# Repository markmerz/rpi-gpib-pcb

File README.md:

# rpi-gpib-pcb
PCB for a Raspberry Pi GPIB board.

Different PCB layout for a electronomikon's Raspberry Pi GPIB shield design at https://github.com/elektronomikon/raspi_gpib_shield/.

This board is 100x100mm and connects to the RPI with 2x20 ribbon cable. Designed to fit into particular milled aluminum box I had lying around. RPI has VXI11 server which exposes GPIB to the network.

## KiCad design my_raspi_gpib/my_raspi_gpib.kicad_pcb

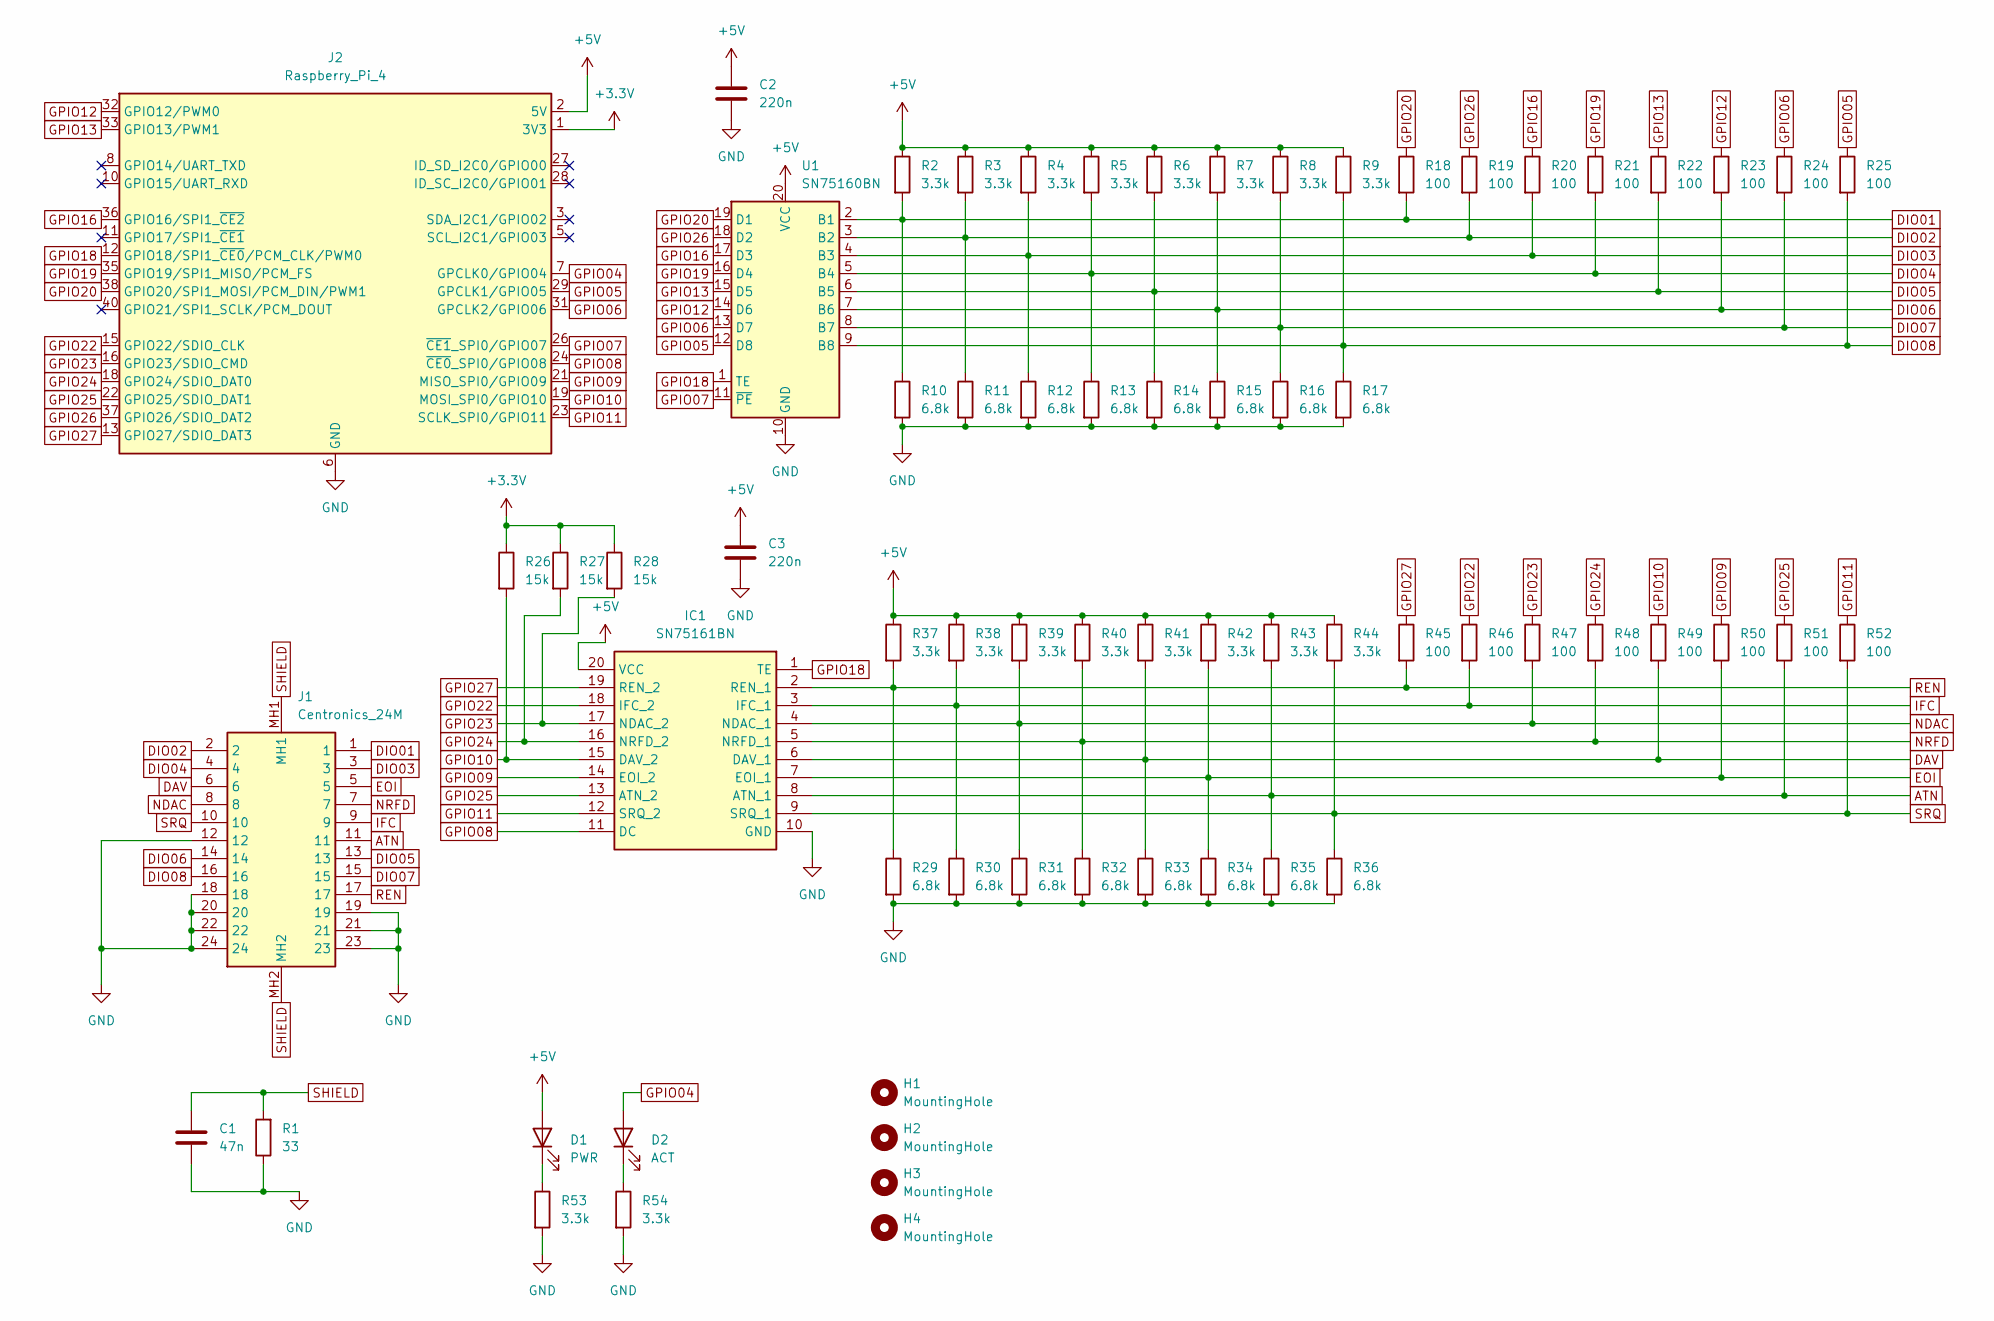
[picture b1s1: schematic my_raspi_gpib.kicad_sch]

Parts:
C1: 47n; C_Disc_D3.8mm_W2.6mm_P2.50mm
C2, C3: 220n; C_Disc_D3.8mm_W2.6mm_P2.50mm
D1: PWR; LED_D3.0mm
D2: ACT; LED_D3.0mm
H1, H2, H3, H4: MountingHole; MountingHole_3.2mm_M3
IC1: SN75161BN; DIP-20_W7.62mm; Manufacturer_Part_Number SN75161BN
J1: Centronics_24M; Manufacturer_Part_Number DS1079-F240BS
J2: Raspberry_Pi_4; PinHeader_2x20_P2.54mm_Vertical
R1: 33; R_Axial_DIN0207_L6.3mm_D2.5mm_P2.54mm_Vertical
R2, R3, R4, R5, R6, R7, R8, R9, R37, R38, R39, R40, R41, R42, R43, R44, R53, R54: 3.3k; R_Axial_DIN0207_L6.3mm_D2.5mm_P2.54mm_Vertical
R10, R11, R12, R13, R14, R15, R16, R17, R29, R30, R31, R32, R33, R34, R35, R36: 6.8k; R_Axial_DIN0207_L6.3mm_D2.5mm_P2.54mm_Vertical
R18, R19, R20, R21, R22, R23, R24, R25, R45, R46, R47, R48, R49, R50, R51, R52: 100; R_Axial_DIN0207_L6.3mm_D2.5mm_P2.54mm_Vertical
R26, R27, R28: 15k; R_Axial_DIN0207_L6.3mm_D2.5mm_P2.54mm_Vertical
U1: SN75160BN; DIP-20_W7.62mm

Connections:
+3.3V: J2.1 (3V3), J2.17 (3V3), R26.1, R27.1, R28.1
+5V: C2.1, C3.1, D1.2 (A), IC1.20 (VCC), J2.2 (5V), J2.4 (5V), R2.1, R3.1, R4.1, R5.1, R6.1, R7.1, R8.1, R9.1, R37.1, R38.1, R39.1, R40.1, R41.1, R42.1, R43.1, R44.1, U1.20 (VCC)
ATN: IC1.8 (ATN_1), J1.11, R35.1, R43.2, R51.2
DAV: IC1.6 (DAV_1), J1.6, R33.1, R41.2, R49.2
DIO01: J1.1, R2.2, R10.1, R18.2, U1.2 (B1)
DIO02: J1.2, R3.2, R11.1, R19.2, U1.3 (B2)
DIO03: J1.3, R4.2, R12.1, R20.2, U1.4 (B3)
DIO04: J1.4, R5.2, R13.1, R21.2, U1.5 (B4)
DIO05: J1.13, R6.2, R14.1, R22.2, U1.6 (B5)
DIO06: J1.14, R7.2, R15.1, R23.2, U1.7 (B6)
DIO07: J1.15, R8.2, R16.1, R24.2, U1.8 (B7)
DIO08: J1.16, R9.2, R17.1, R25.2, U1.9 (B8)
EOI: IC1.7 (EOI_1), J1.5, R34.1, R42.2, R50.2
GND: C1.1, C2.2, C3.2, IC1.10 (GND), J1.12, J1.18, J1.19, J1.20, J1.21, J1.22, J1.23, J1.24, J2.6 (GND), J2.9 (GND), J2.14 (GND), J2.20 (GND), J2.25 (GND), J2.30 (GND), J2.34 (GND), J2.39 (GND), R1.1, R10.2, R11.2, R12.2, R13.2, R14.2, R15.2, R16.2, R17.2, R29.2, R30.2, R31.2, R32.2, R33.2, R34.2, R35.2, R36.2, R53.2, R54.2, U1.10 (GND)
GPIO02: J2.3 (SDA_I2C1/GPIO02)
GPIO03: J2.5 (SCL_I2C1/GPIO03)
GPIO04: D2.2 (A), J2.7 (GPCLK0/GPIO04)
GPIO05: J2.29 (GPCLK1/GPIO05), R25.1, U1.12 (D8)
GPIO06: J2.31 (GPCLK2/GPIO06), R24.1, U1.13 (D7)
GPIO07: J2.26 (~CE1_SPI0/GPIO07), U1.11 (~PE)
GPIO08: IC1.11 (DC), J2.24 (~CE0_SPI0/GPIO08)
GPIO09: IC1.14 (EOI_2), J2.21 (MISO_SPI0/GPIO09), R50.1
GPIO10: IC1.15 (DAV_2), J2.19 (MOSI_SPI0/GPIO10), R26.2, R49.1
GPIO11: IC1.12 (SRQ_2), J2.23 (SCLK_SPI0/GPIO11), R52.1
GPIO12: J2.32 (GPIO12/PWM0), R23.1, U1.14 (D6)
GPIO13: J2.33 (GPIO13/PWM1), R22.1, U1.15 (D5)
GPIO14: J2.8 (GPIO14/UART_TXD)
GPIO15: J2.10 (GPIO15/UART_RXD)
GPIO16: J2.36 (GPIO16/SPI1_~CE2), R20.1, U1.17 (D3)
GPIO17: J2.11 (GPIO17/SPI1_~CE1)
GPIO18: IC1.1 (TE), J2.12 (GPIO18/SPI1_~CE0/PCM_CLK/PWM0), U1.1 (TE)
GPIO19: J2.35 (GPIO19/SPI1_MISO/PCM_FS), R21.1, U1.16 (D4)
GPIO20: J2.38 (GPIO20/SPI1_MOSI/PCM_DIN/PWM1), R18.1, U1.19 (D1)
GPIO21: J2.40 (GPIO21/SPI1_SCLK/PCM_DOUT)
GPIO22: IC1.18 (IFC_2), J2.15 (GPIO22/SDIO_CLK), R46.1
GPIO23: IC1.17 (NDAC_2), J2.16 (GPIO23/SDIO_CMD), R28.2, R47.1
GPIO24: IC1.16 (NRFD_2), J2.18 (GPIO24/SDIO_DAT0), R27.2, R48.1
GPIO25: IC1.13 (ATN_2), J2.22 (GPIO25/SDIO_DAT1), R51.1
GPIO26: J2.37 (GPIO26/SDIO_DAT2), R19.1, U1.18 (D2)
GPIO27: IC1.19 (REN_2), J2.13 (GPIO27/SDIO_DAT3), R45.1
IFC: IC1.3 (IFC_1), J1.9, R30.1, R38.2, R46.2
NDAC: IC1.4 (NDAC_1), J1.8, R31.1, R39.2, R47.2
NRFD: IC1.5 (NRFD_1), J1.7, R32.1, R40.2, R48.2
unnamed: D1.1 (K), R53.1
unnamed: D2.1 (K), R54.1
REN: IC1.2 (REN_1), J1.17, R29.1, R37.2, R45.2
SHIELD: C1.2, J1.MH1, J1.MH2, R1.2
SRQ: IC1.9 (SRQ_1), J1.10, R36.1, R44.2, R52.2

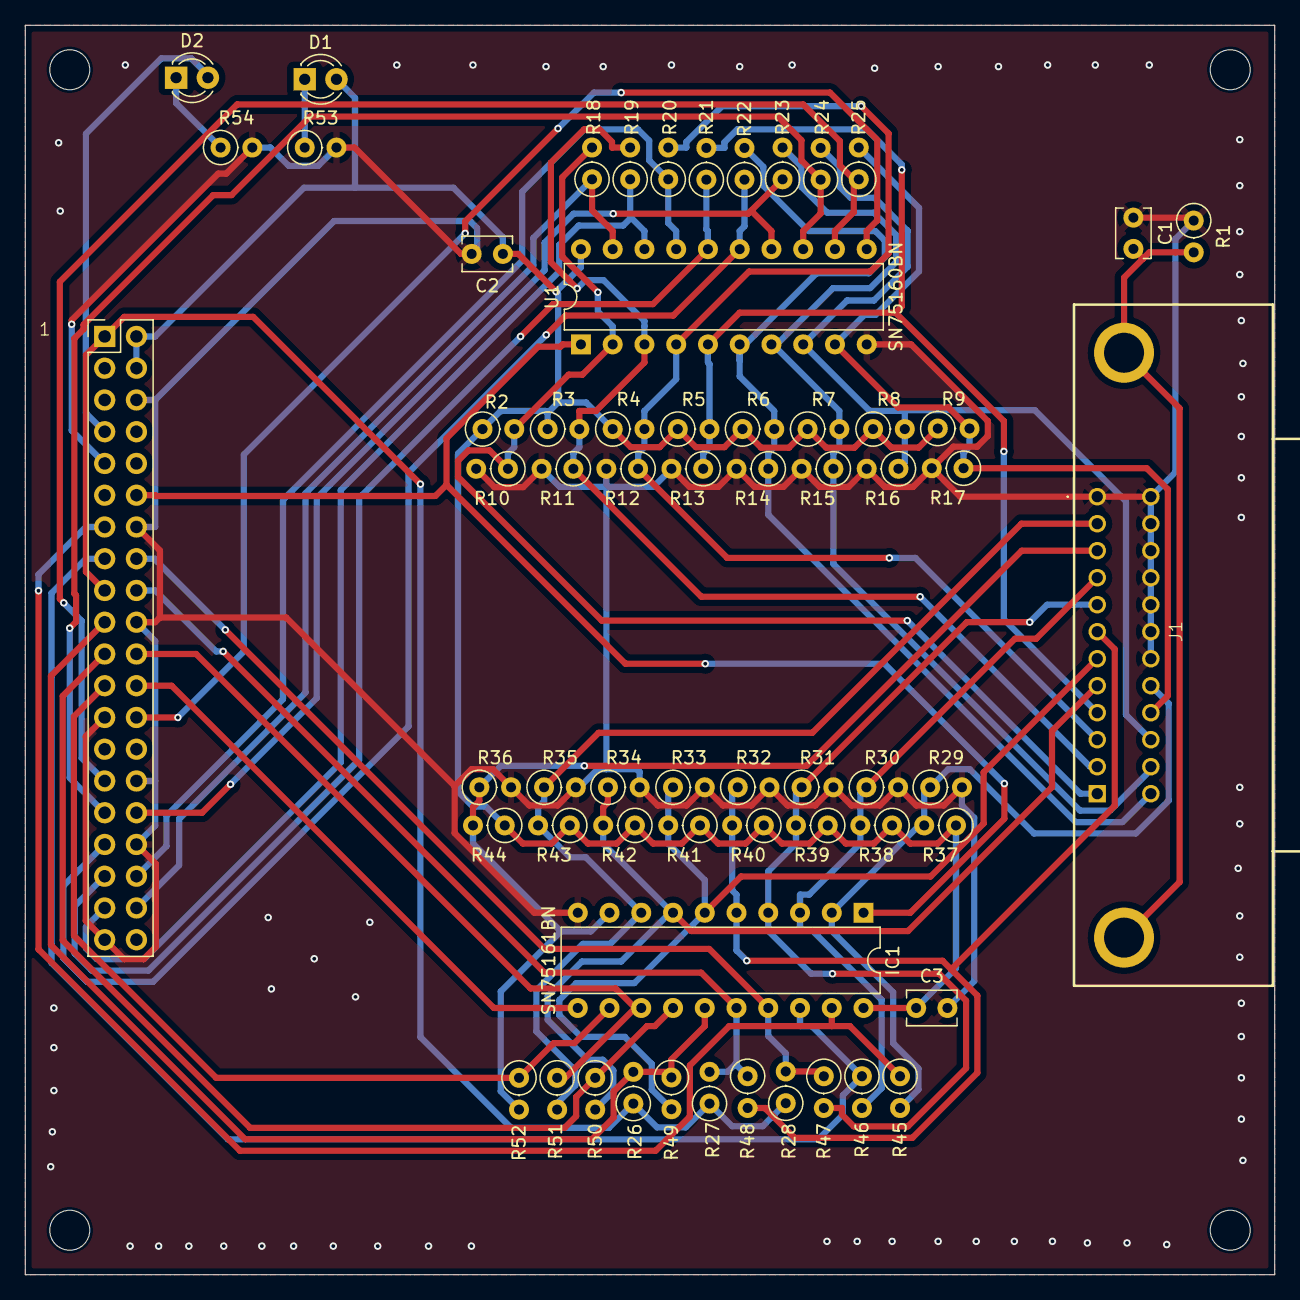
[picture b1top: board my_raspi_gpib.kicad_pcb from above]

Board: 2 copper layers, 99.9 x 99.9 mm, 67 parts (0 on the bottom side), 42 nets.

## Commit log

2025-03-15 Import
